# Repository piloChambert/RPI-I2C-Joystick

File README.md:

# RPI-I2C-Joystick

I2C Arduino based joystick for Raspberry Pi in order to be used with [RetroPie](https://github.com/RetroPie/RetroPie-Setup).
The Arduino is also used to control audio volume and power management (switch the Raspberry Pi on and off).

## Aruino

- The arduino (an ATMega328 running with its internal 8Mhz clock) is used to control the Raspberry Pi. It's used to read joystick buttons and analog axis. 
- The [board](https://github.com/piloChambert/RPI-I2C-Joystick/board) directory contains the schematic (and pcb), compatible with raspberry Pi GPIO. THIS IS A WORK IN PROGRESS!!! By now it's tested on a breadboard.
- The [i2c_gamepad](https://github.com/piloChambert/RPI-I2C-Joystick/i2c_gamepad) directory contains the actual arduino code. 

### hardware

The [hardware](https://github.com/piloChambert/RPI-I2C-Joystick/tree/master/hardware) directory contains the definition for the ATMega328 without quartz configuration (and PINB6 and PINB7 enable).

## Raspberry Pi

### power

In order to know when the raspberry pi has been shutdown, the gpio-poweroff overlay is used. This is the /kill signal going to the arduino (HIGH when the raspberry pi is halted).

In /boot/config.txt:
```
dtoverlay=gpio-poweroff,gpiopin=4,active_low="y"
```

### joystick

The [driver](https://github.com/piloChambert/RPI-I2C-Joystick/driver) directory contains the code of the user space uinput driver for the arduino I2C joystick.

### Display Configuration

I use a 4.3" 480x272 TFT display using composite video (maybe the worst quality possible). It would be better to use a DPI interface (with the GPIO, an HDMI to DPI converter, or a DSI to DPI converter).

Here's my video and overscan settings in `/boot/config.txt`
```
disable_overscan=1

overscan_left=34
overscan_right=20
overscan_top=16
overscan_bottom=20
overscan_scale=1

# set the frame buffer to match the tft resolution
framebuffer_width=480
framebuffer_height=272
framebuffer_depth=24

# use PAL, it seems way better than NTSC!!
sdtv_mode=2

# 16:9 aspect
sdtv_aspect=3

```

In order to setup the overscan settings, I used https://github.com/popcornmix/set_overscan, and then tweaked the values by hand.

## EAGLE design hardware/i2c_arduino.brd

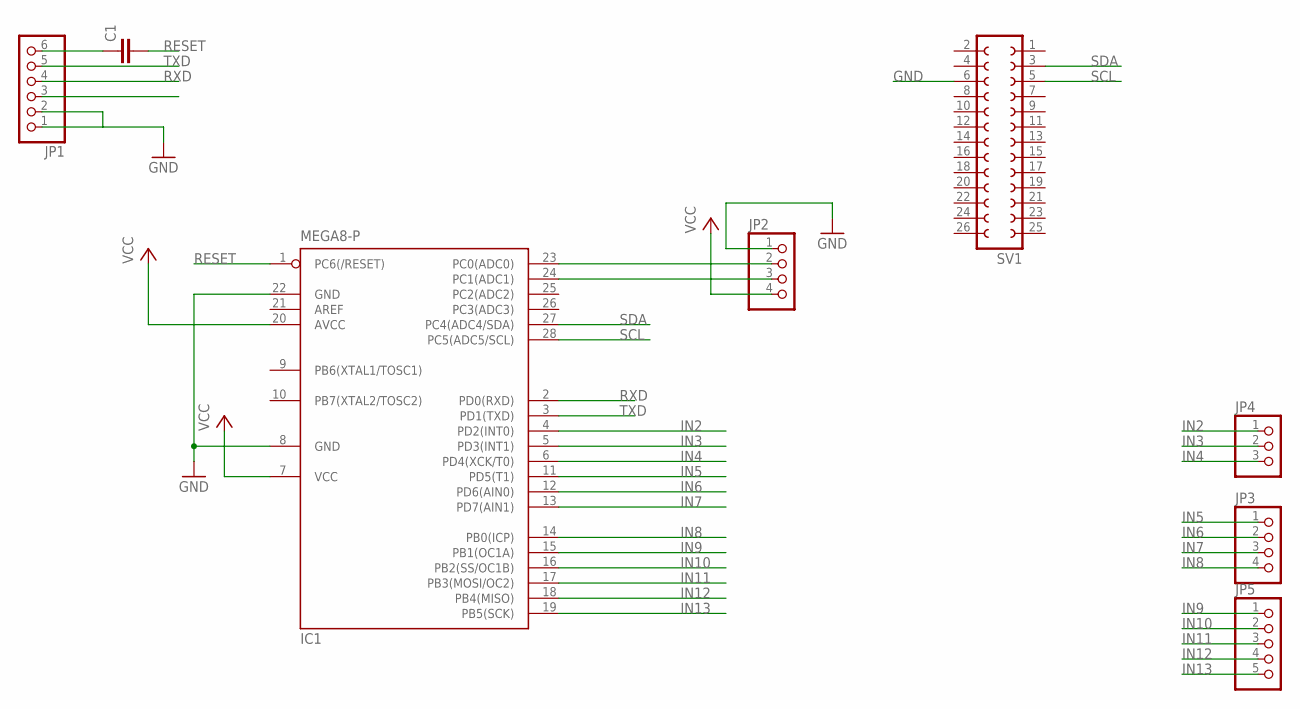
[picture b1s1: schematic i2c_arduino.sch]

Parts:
C1: C-EU025-025X050; C025-025X050
IC1: MEGA8-P; DIL28-3
JP1: PINHD-1X6/90; 1X06/90
JP2, JP3: PINHD-1X4; 1X04
JP4: PINHD-1X3; 1X03
JP5: PINHD-1X5; 1X05
SV1: FE13-2

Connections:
GND: IC1.8 (GND), IC1.22 (GND), JP1.1, JP1.2, JP2.1, SV1.6
IN2: IC1.4 (PD2(INT0)), JP4.1
IN3: IC1.5 (PD3(INT1)), JP4.2
IN4: IC1.6 (PD4(XCK/T0)), JP4.3
IN5: IC1.11 (PD5(T1)), JP3.1
IN6: IC1.12 (PD6(AIN0)), JP3.2
IN7: IC1.13 (PD7(AIN1)), JP3.3
IN8: IC1.14 (PB0(ICP)), JP3.4
IN9: IC1.15 (PB1(OC1A)), JP5.1
IN10: IC1.16 (PB2(SS/OC1B)), JP5.2
IN11: IC1.17 (PB3(MOSI/OC2)), JP5.3
IN12: IC1.18 (PB4(MISO)), JP5.4
IN13: IC1.19 (PB5(SCK)), JP5.5
unnamed: C1.1, JP1.6
unnamed: IC1.23 (PC0(ADC0)), JP2.2
unnamed: IC1.24 (PC1(ADC1)), JP2.3
RESET: C1.2, IC1.1 (PC6(/RESET))
RXD: IC1.2 (PD0(RXD)), JP1.4
SCL: IC1.28 (PC5(ADC5/SCL)), SV1.5
SDA: IC1.27 (PC4(ADC4/SDA)), SV1.3
TXD: IC1.3 (PD1(TXD)), JP1.5
VCC: IC1.7 (VCC), IC1.20 (AVCC), JP1.3, JP2.4

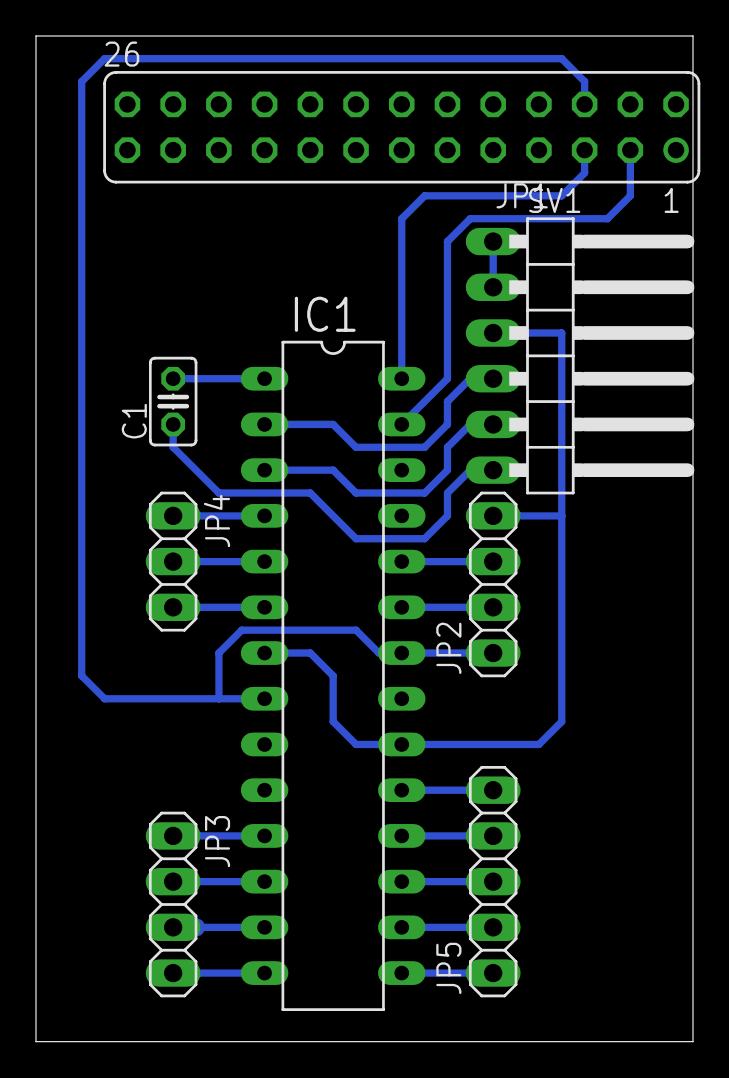
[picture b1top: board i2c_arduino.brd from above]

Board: 2 copper layers, 36.5 x 55.9 mm, 8 parts (0 on the bottom side), 22 nets.

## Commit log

2015-09-20 Added rpi driver
2015-09-20 added arduino project
2015-09-20 small changes
2015-09-20 Put driver in its directory
2015-09-20 Updated RPI driver
2015-09-20 Updated arduino code to handle switch
2015-09-20 Added schematic and pcb
2015-09-20 removed eagle tmp file
2015-09-22 Updated buttons handling
2015-09-24 Added analog support
2015-09-24 Updated I2C driver, added blob with KILL signal
2015-09-25 Updated arduino code Removed blob (not used anymore)
2015-09-25 fixed arduino code
2015-09-26 Added sleep mode test on arduino Added Arduino wiring drawing
2015-09-27 Added png version of arduino wiring
2015-09-27 Updated Arduino wiring
2015-09-27 Added shutdown with pwr switch refactorcode
2015-09-27 Added audio volume control
2015-10-04 added cae design
2015-10-13 Minor fixes
2015-10-13 Added documentation directory
2015-10-19 Added hat control
2015-11-03 updated case design
2015-12-02 added case design
2015-12-31 added states
2015-12-31 updated case
2016-02-07 Updated arduino states
2020-08-26 Create LICENSE
2020-08-26 Update LICENSE
2020-09-09 Added configuration defines
2020-09-10 Added dpad event in joystick driver
2021-05-24 hardware images and organzie headers (#4)
